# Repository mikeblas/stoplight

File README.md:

# stoplight
This project provides hardware and software for a stoplight controlled by a Raspberry Pi.

## Context
In the late 1990s, I purchased a traffic signal from a curiosities shop. It's a full-scale signal, appropriate for
"real" outdoor use; each lens is about 20cm in diameter, and it's a giant green beast. During the lockdowns in 2020,
I finally found the time to get it working in a fun and useful way.

This project includes a printed circuit board design that hosts a Raspberry Pi Zero W and implements a
mains-based power supply and switching circuits for each of the lamps in the signal. I chose the Pi Zero because
it gets me onto the wireless network, and has enough computing power to do interesting things with the signal. With
a little research, it should be possible to find a smaller board that has WiFi connectivity, but I already had an
unused Pi Zero, so I just went with it.

The board further hosts a generic wireless remote control board built around the PT2272 receiver chip. The chip
gives four latched outputs from a four-button key fob style RF remote. This remote can be used to control
the stoplight.

And of course, the project includes software to make it do something.

## Status

This project is "done enough" for now. All the features below are implemented, and the wish list features are
not yet implemented.

## Hardware Features

The hardware is done; amazingly, I didn't have to re-print the board and got it right on the first try. The
only problem was using a 7805 regulator. The voltage drop made it run red hot, so I replaced it with a three-pin
PC-based switching regulator, which works fine. The filter capacitor on the output of the supply wasn't adequate,
so I increased it. That, of course, required a part with a bigger footprint so the mounting is a bit lumpy,
but it works fine.

## Software Features

The software implements several modes, selectable by the remote. First, we can turn the thing off:

* Turn off the light; minimal processing, nothing illuminated.
* Turn the light back on; whatever mode was active last resumes.

Then, we have one of a few modes active:

* Traffic light. Red, green, yellow, in a realistically timed cycle.
* Random single flash. Flash a single (selectable) lamp at a regular interval.
* Random flash. Flash a randomly selected lamp one at a time.
* Random flash. Flash each lamp at random intervals. This is "disco mode"! 
* Manual selection. Turn a lamp off or on, and it stays that way.

We mostly leave the light in disco mode, and it's fun to see it blinking away.

## Wish List

I'd like to add a few more modes:

* Clock. Flash lights to make a binary time-of-day clock.
* Weather indicator. Show tomorrow's predicted weather (temperature and precipitation)
* Stock market indicator. If the market is open, show the directional change in a particular index.

There's also a couple of interesting things that I'd like to add:

* Mode memory. It would be great to have the system restore its mode when it starts up again after
a reboot or power failure.
* Monitoring. Anything I can monitor in my home network is monitored -- lots of SNMP collectors and
some Influx scripts pull data in to Grafana. Adding 
* Web page. It would be cool to have a little web server to present a UI for changing modes, looking
at statistics, and so on.
* Mobile app. A web API would enable a mobile application for modes and stats, too.

Since the project is built and installed, then I'm not very motivated to work on these things. Maybe
in the winter I'll get another Pi Zero and set it up so I can run the core on my bench, and get to
work on those feature. The design has on-board LEDs for all of the outputs, so pretty much no support
circuitry is necessary. I just need to build and populate one of my spare PC boards. 

## Project Layout

`stoplightd` is the stoplight daemon program. This is the controller that runs on the Pi (as I'm working on it)

`proto` are various fragments and scratch projects as I sort out GPIO, how the hardware works, and try out ideas.

`pcb` is the hardware project for KiCad.

## Images

Installing KiCad just to take a peek is a big ask, so here are some links:

* A snapshot of [the PC board](docs/pics/pc_board.png "PC Board")
* A snapshot of [the schematic](docs/pics/schematic.png "Schematic")

# Dependencies

This project uses [libdaemonize](https://github.com/Aethelflaed/libdaemonize).

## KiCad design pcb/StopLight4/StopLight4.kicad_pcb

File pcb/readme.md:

# Stoplight Controller PC Board

This directory contains different versions of the StopLight PC Board. I split the design since I wasn't comfortable using `git` to manage the projects, and I also wasn't positive I wouldn't fork or rework the older designs anyway. I ended up linear, though, and StopLight4 is the version of the board sent to be fabricated.

## StopLight1

Uses discrete transistors to drive the relays and indicator LEDs.

## StopLight2

Substitutes a `ULN2803` driver chip for the relays to save a lot of space.

## StopLight3

Relays turned out to be pretty noisy, so I built a TRIAC circuit to drive the lights. Maybe the `ULN2803` isn't necessary anymore, but it remains. (Uhoh. Looks like some files are missing!)

## StopLight4

There were fuses on each of the three light lines, which is a bit redundant. Seems nice, but the fuse holders take up a ton of PC board space so I've eliminated them. This resulted in a more pleasing layout and a smaller board. This board version was sent to production.

## StopLight5

This version will fix a few issues, if another production run is needed:

1) Holes in remote header too smaller (0.75mm, should be 1.00mm)
2) Phoenix connectors are facing the wrong way
3) Rotate TP5 so its silk screen matches other TPs
4) Mask over the copper legend for high-voltage outputs
5) "hash" silkscreen over high voltage area of board
6) Renumber F4 to F1

# Hardware PostMortem

Most of the interesting problems are listed above, but some are not; and some are interesting to investigate a little more.

## Power Supply

Most of the issues were with the power supply, really.

**Power Budget**. I just figured I'd get a transformer, rectifier, a couple of filter caps, and drive a 7805 and be done. It's a little more complicated than that. First off, I bugeted a bit high for power because I thought I would be holding relays up. Once I eliminated the relays, I shouldn't made a closer estimate. The supply should drive about 1.5 amps without a problem (except for heat), and I could use a much smaller transformer since my budget is really closer to 500 milliamps.

**Filter**. I couldn't find good advice about sizing the filter caps, and they're too small. Maybe the over-arching problem is that I didn't prototype the power supply on my breadboard. Had I done so, I would've caught most (if not all) of these problems.

**Heat**. My transformer develops 10 volts at the secondary, which initially sounded low. The dropout of the regulator means I need at least 7 volts at the input, and I'm making lots of heat in the linear regulator. A switching regulator is probably the best solution, and I'm probably going to end up getting one of the "cheater" switching converters on a TO-220-sized board to solve the heat issue.

## Layout

I'm pretty pleased with the layout. I was always tempted to "hide" components under the Raspberry Pi module, but I'm glad I didn't because it would  have made troubleshooting harder. Getting a probe onto anything under there would be obnoxious -- my only choice would be to get to the back of the board.

After that, the layout is pretty nice. I'm glad I got rid of the redundant fuses. It might have helped more the use an in-line fuse holder, but those also have some inconveniences. A smaller fuse form factor might have been a good idea, tho.

## In General

It was great to get rid of the relays. The clicking was completely obnoxious; I can't imagine these being used in anything but an industrial or large commercial application. Learning how to control the TRIACS was fun. 

I could probably get rid of the driver, but it's not much real estate and gives me a bit more confidence in the design for now.

## Software

The software is going well, though I don't have as much time to spend on it. When I do, I'm productive and can get some things done.

## Mechanical

The mechanical assembly came together quite well, and I'm happy with it. Even the carpentry isn't so bad.

## Light Bulbs

I'm worried that the light is too bright. Maybe a cool V2 feature would be to support PWM dimming so the brightness would be settable through software. Choosing bulbs was hard; there aren't many incadescent choices anymore. LED bulbs don't go so dim, either. The 25-watt equivalent LED bulb seems best, but it's quite expensive (about $8) and who knows how long they'll make it. A couple LED bulbs I tried didn't turn on or off correctly, so experimenting is kind of hit-and-miss.

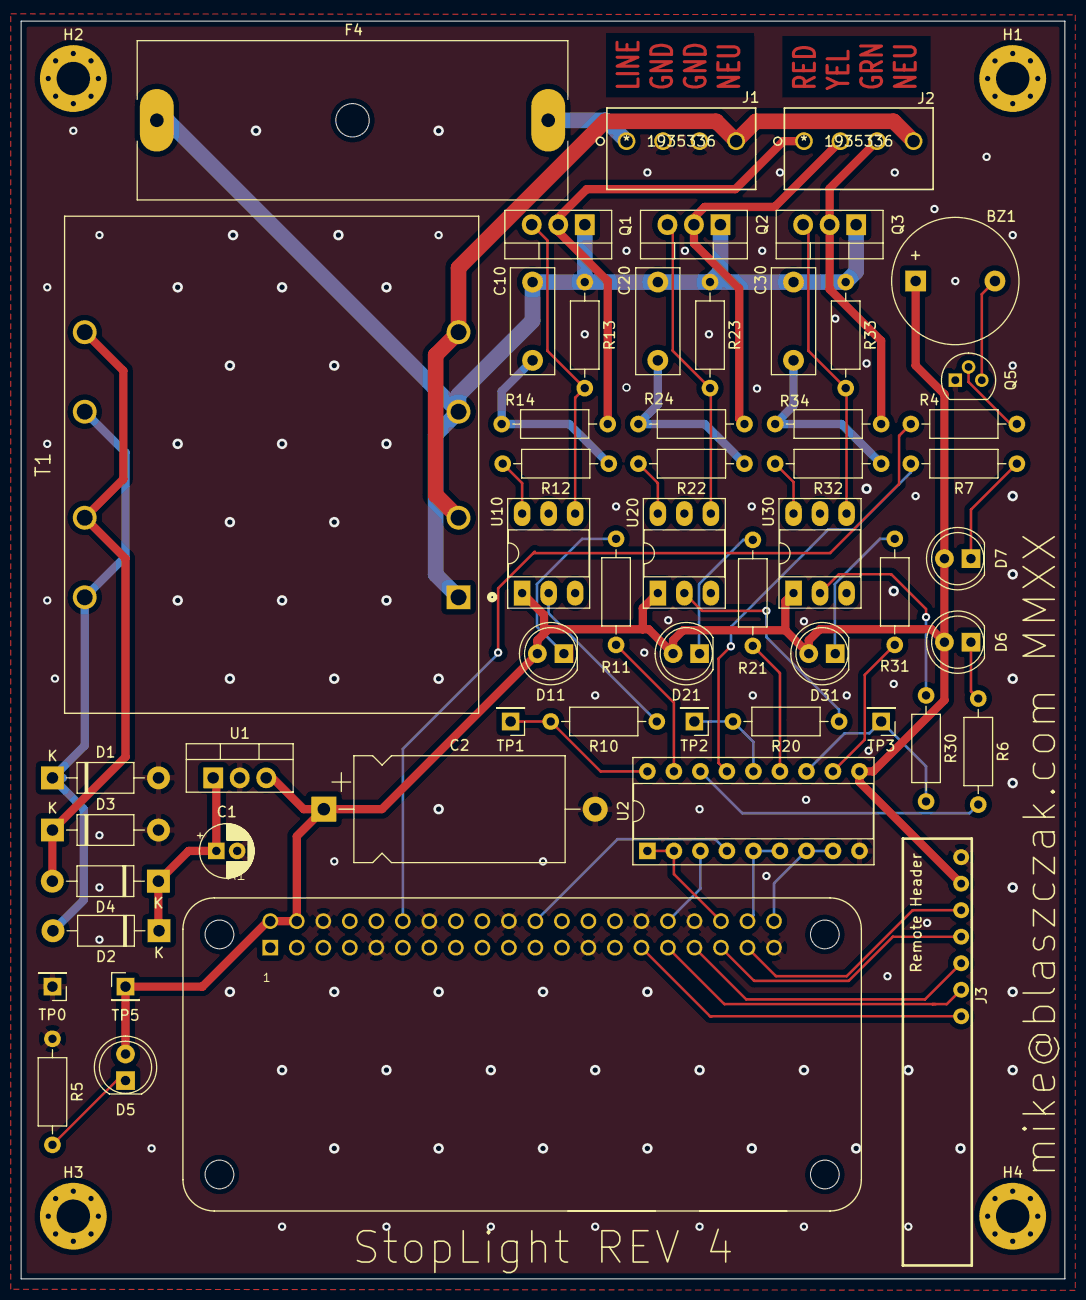
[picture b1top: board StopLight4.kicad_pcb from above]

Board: 2 copper layers, 100.0 x 120.5 mm, 59 parts (0 on the bottom side), 50 nets.

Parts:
A1: ADA3708; ADA3708_RPI-ZERO
BZ1: Buzzer; Buzzer_12x9.5RM7.6
C1: 3.3uF; CP_Radial_D5.0mm_P2.00mm
C2: 220uF 50v; CP_Axial_L20.0mm_D10.0mm_P26.00mm_Horizontal
C10, C20, C30: 0.033uF; C_Rect_L10.0mm_W4.0mm_P7.50mm_MKS4
D1, D2, D3, D4: 1N4002; D_DO-41_SOD81_P10.16mm_Horizontal
D5, D6, D7, D11, D21, D31: LED; LED_D5.0mm
F4: Fuse; Fuseholder_Cylinder-6.3x32mm_Schurter_0031-8002_Horizontal_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
H1, H2, H3, H4: MountingHole; MountingHole_3.2mm_M3_Pad_Via
J1, J2: 1935336; 1984633
J3: Remote Header; WirelessRemote
Q1, Q2, Q3: BT136-600; TO-220-3_Vertical
Q5: 2N3904; TO-92
R4: 10R3; R_Axial_DIN0207_L6.3mm_D2.5mm_P10.16mm_Horizontal
R5, R6, R7, R10, R11, R20, R21, R30, R31: 220R; R_Axial_DIN0207_L6.3mm_D2.5mm_P10.16mm_Horizontal
R12, R22, R32: 150R; R_Axial_DIN0207_L6.3mm_D2.5mm_P10.16mm_Horizontal
R13, R23, R33: 390R; R_Axial_DIN0207_L6.3mm_D2.5mm_P10.16mm_Horizontal
R14, R24, R34: 51R; R_Axial_DIN0207_L6.3mm_D2.5mm_P10.16mm_Horizontal
T1: FS20-600; XFMR_FS20-600
TP0, TP1, TP2, TP3, TP5: Conn_01x01_Male; PinHeader_1x01_P2.54mm_Vertical
U1: L7805; TO-220-3_Vertical
U2: ULN2803A; DIP-18_W7.62mm_Socket
U10, U20, U30: MOC3021M; DIP-6_W7.62mm_Socket_LongPads

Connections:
/D0: A1.37, J3.5
/D1: A1.35, J3.4
/D2: A1.33, J3.3
/D3: A1.31, J3.2
/GRN: A1.40, U2.7, U2.8
/IND1: A1.32, U2.3
/IND2: A1.22, U2.4
/RED: A1.36, U2.1, U2.2
/VT: A1.29, J3.1
/YEL: A1.38, U2.5, U2.6
BZZ: A1.12, R4.2
GND: A1.6, A1.9, A1.14, A1.20, A1.25, A1.30, A1.34, A1.39, C1.2, C2.2, D1.2, D3.2, J1.2, J1.3, J3.7, Q5.1, R5.1, TP0.1, U1.2, U2.9
LINE: C10.2, C20.2, C30.2, F4.1, Q1.1, Q2.1, Q3.1, R13.1, R23.1, R33.1, T1.1, T1.3
NEUT: J1.4, J2.4, T1.2, T1.4
unnamed: BZ1.2, Q5.3
unnamed: C1.1, D2.1, D4.1, U1.1
unnamed: C10.1, R12.1, R14.2
unnamed: C20.1, R22.1, R24.2
unnamed: C30.1, R32.1, R34.2
unnamed: D1.1, D2.2, T1.5, T1.7
unnamed: D3.1, D4.2, T1.6, T1.8
unnamed: D5.1, R5.2
unnamed: D6.1, R6.1
unnamed: D7.1, R7.1
unnamed: D11.1, R11.1
unnamed: D21.1, R21.1
unnamed: D31.1, R31.1
unnamed: J2.1, Q1.2, R14.1
unnamed: J2.2, Q2.2, R24.1
unnamed: J2.3, Q3.2, R34.1
unnamed: Q1.3, R13.2, U10.4
unnamed: Q2.3, R23.2, U20.4
unnamed: Q3.3, R33.2, U30.4
unnamed: Q5.2, R4.1
unnamed: R6.2, U2.16
unnamed: R7.2, U2.15
unnamed: R10.1, U10.2
unnamed: R10.2, TP1.1, U2.18
unnamed: R11.2, U2.17
unnamed: R12.2, U10.6
unnamed: R20.1, U20.2
unnamed: R20.2, TP2.1, U2.14
unnamed: R21.2, U2.13
unnamed: R22.2, U20.6
unnamed: R30.1, U30.2
unnamed: R30.2, TP3.1, U2.12
unnamed: R31.2, U2.11
unnamed: R32.2, U30.6
VAC: F4.2, J1.1
VCC: A1.2, A1.4, BZ1.1, C2.1, D5.2, D6.2, D7.2, D11.2, D21.2, D31.2, J3.6, TP5.1, U1.3, U2.10, U10.1, U20.1, U30.1

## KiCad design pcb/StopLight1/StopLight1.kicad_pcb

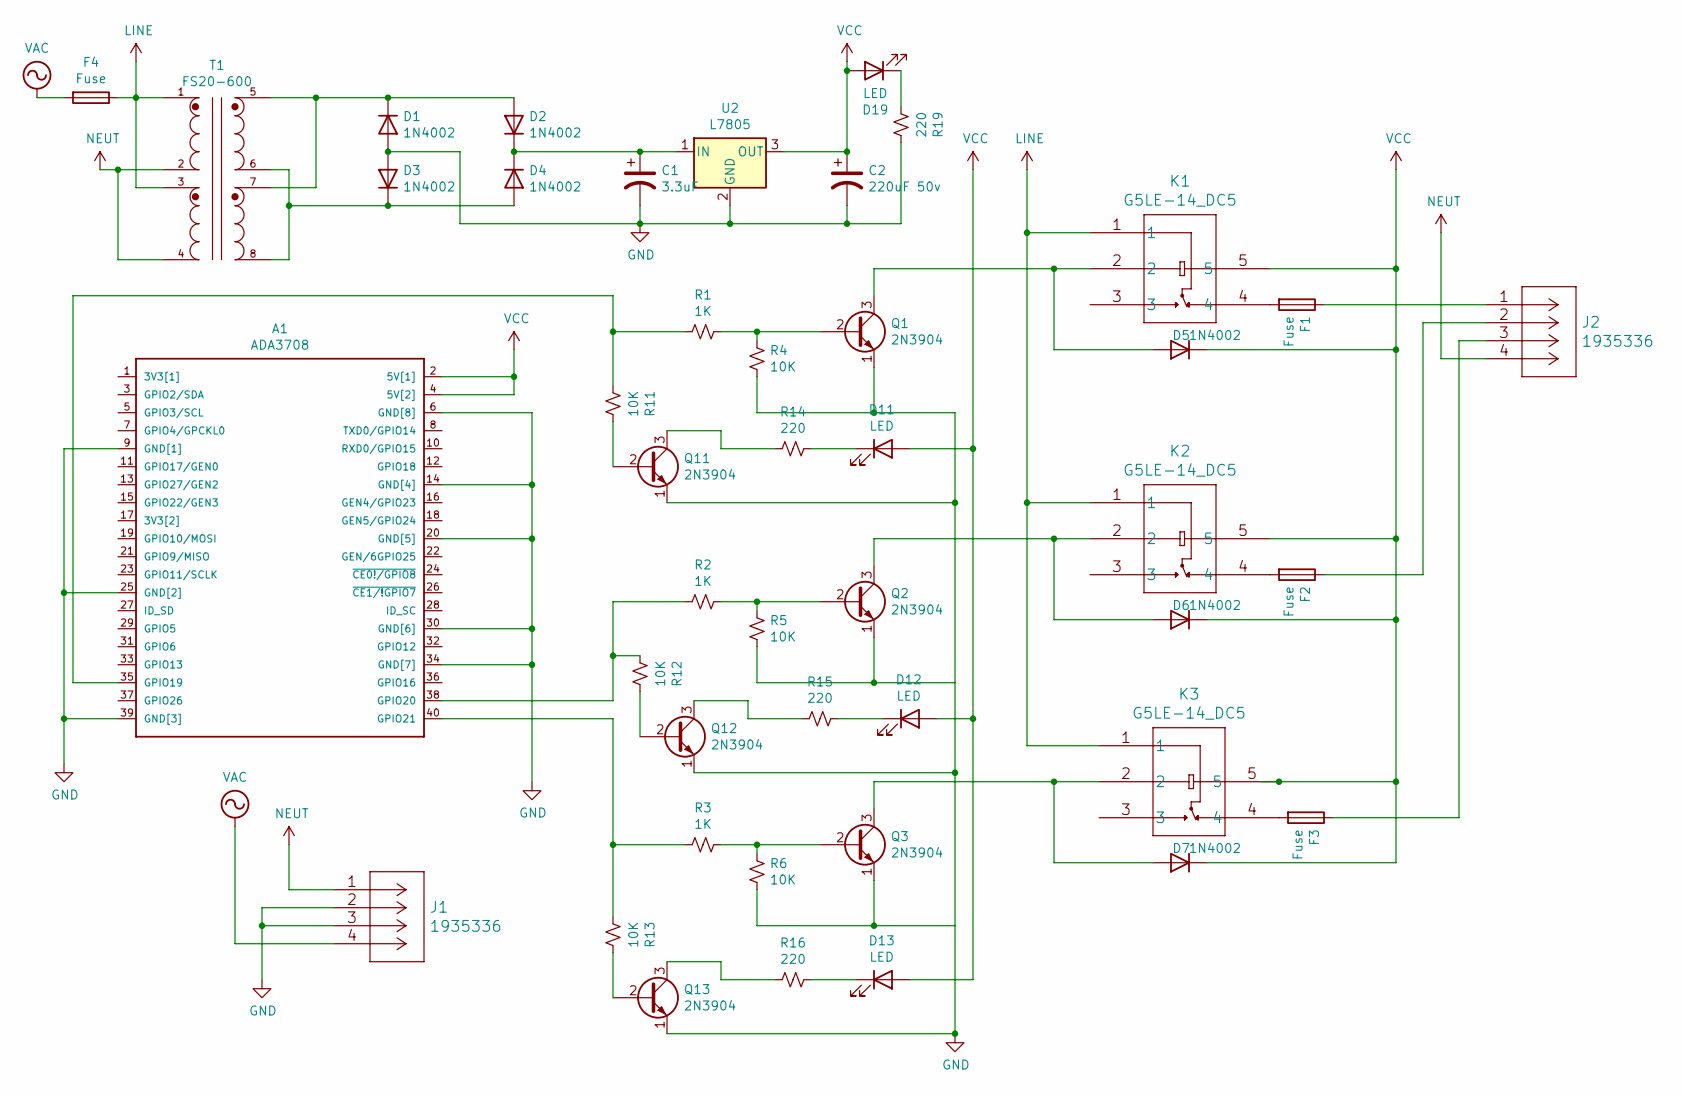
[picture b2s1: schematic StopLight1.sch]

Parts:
A1: ADA3708; ADA3708_RPI-ZERO
C1: 3.3uF; CP_Radial_D5.0mm_P2.00mm
C2: 220uF 50v; CP_Axial_L20.0mm_D10.0mm_P26.00mm_Horizontal
D1, D2, D3, D4, D5, D6, D7: 1N4002; D_DO-41_SOD81_P10.16mm_Horizontal
D11, D12, D13, D19: LED; LED_D5.0mm
F1, F2, F3, F4: Fuse; Fuseholder_Cylinder-6.3x32mm_Schurter_0031-8002_Horizontal_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
J1, J2: 1935336
K1, K2, K3: G5LE-14_DC5; G5LE-14 DC5
Q1, Q2, Q3, Q11, Q12, Q13: 2N3904; TO-92
R1, R2, R3: 1K; R_Axial_DIN0207_L6.3mm_D2.5mm_P10.16mm_Horizontal
R4, R5, R6, R11, R12, R13: 10K; R_Axial_DIN0207_L6.3mm_D2.5mm_P10.16mm_Horizontal
R14, R15, R16, R19: 220; R_Axial_DIN0207_L6.3mm_D2.5mm_P10.16mm_Horizontal
T1: FS20-600; XFMR_FS20-600
U2: L7805; TO-220-3_Vertical

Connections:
GND: A1.6 (GND[8]), A1.9 (GND[1]), A1.14 (GND[4]), A1.20 (GND[5]), A1.25 (GND[2]), A1.30 (GND[6]), A1.34 (GND[7]), A1.39 (GND[3]), C1.2, C2.2, D1.2 (A), D3.2 (A), J1.2, J1.3, Q1.1 (E), Q11.1 (E), Q12.1 (E), Q13.1 (E), R4.2, R19.1, U2.2 (GND)
LINE: F4.1, K1.1, K2.1, K3.1, T1.1, T1.3
NEUT: J1.1, J2.4, T1.2, T1.4
unnamed: A1.35 (GPIO19), R1.2, R11.2
unnamed: A1.38 (GPIO20), R2.2, R12.2
unnamed: A1.40 (GPIO21), R3.2, R13.2
unnamed: C1.1, D2.1 (K), D4.1 (K), U2.1 (IN)
unnamed: D1.1 (K), D2.2 (A), T1.5, T1.7
unnamed: D3.1 (K), D4.2 (A), T1.6, T1.8
unnamed: D5.2 (A), K1.2, Q1.3 (C)
unnamed: D6.2 (A), K2.2, Q2.3 (C)
unnamed: D7.2 (A), K3.2, Q3.3 (C)
unnamed: D11.1 (K), R14.1
unnamed: D12.1 (K), R15.1
unnamed: D13.1 (K), R16.1
unnamed: D19.1 (K), R19.2
unnamed: F1.1, J2.1
unnamed: F1.2, K1.4
unnamed: F2.1, J2.2
unnamed: F2.2, K2.4
unnamed: F3.1, J2.3
unnamed: F3.2, K3.4
unnamed: Q1.2 (B), R1.1, R4.1
unnamed: Q2.1 (E), R5.2
unnamed: Q2.2 (B), R2.1, R5.1
unnamed: Q3.1 (E), R6.2
unnamed: Q3.2 (B), R3.1, R6.1
unnamed: Q11.2 (B), R11.1
unnamed: Q11.3 (C), R14.2
unnamed: Q12.2 (B), R12.1
unnamed: Q12.3 (C), R15.2
unnamed: Q13.2 (B), R13.1
unnamed: Q13.3 (C), R16.2
VAC: F4.2, J1.4
VCC: A1.2 (5V[1]), A1.4 (5V[2]), C2.1, D5.1 (K), D6.1 (K), D7.1 (K), D11.2 (A), D12.2 (A), D13.2 (A), D19.2 (A), K1.5, K2.5, K3.5, U2.3 (OUT)

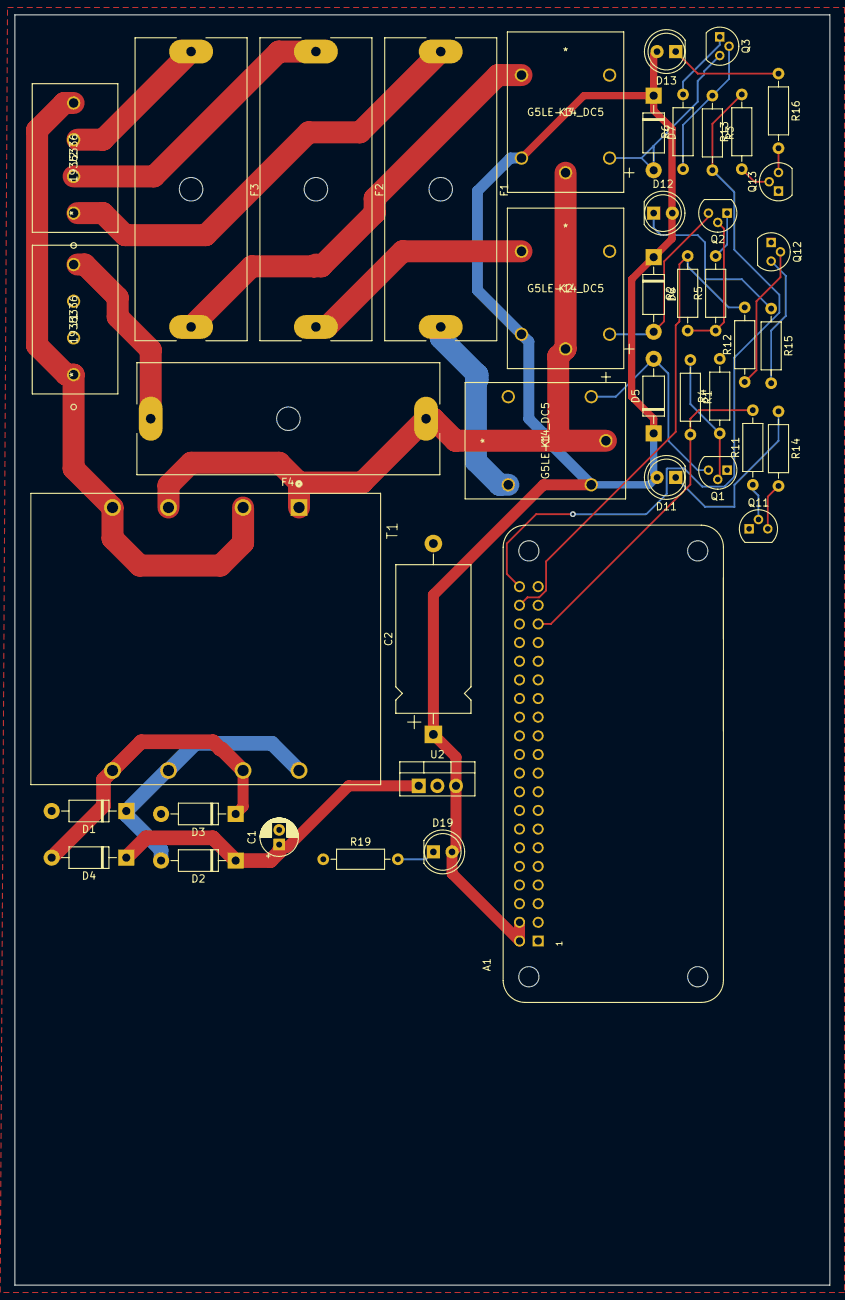
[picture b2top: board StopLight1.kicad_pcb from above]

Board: 2 copper layers, 111.0 x 173.0 mm, 44 parts (0 on the bottom side), 35 nets.

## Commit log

2020-09-03 get something into the readme
2020-09-03 add PCB projects
2020-09-03 add first GPIO app
2020-09-03 first cut at remote reading
2020-09-03 only show when change detected
2020-09-04 try using wait functions for remote input
2020-09-06 remove commented code
2020-09-06 add flick program
2020-09-06 PC Board design is getting close
2020-09-09 Smaller PCB, sent to production!
2020-09-09 add readme files, restructure directories
2020-09-09 delay to let remote inputs stabilize
2020-09-09 controllable with remote
2020-09-09 beep feedback
2020-09-10 tighten up makefiles
2020-09-10 add gitignore files
2020-09-11 first cut at a daemon
2020-09-13 turn on warnings, fix them up
2020-09-13 note dependency
2020-09-17 setup stoplightd daemon project
2020-09-17 readme about the plan
2020-09-17 handle press/release in framework loop
2020-09-17 one step closer
2020-09-17 cleanup, fix gitignore
2020-09-17 update readme, refactor modelinterface header
2020-09-17 fix gitignore, clean up makefile a bit
2020-09-17 add selector mode for testing; some makefile tweaks
2020-09-17 refactor daemon itself, fix up makefile, split function
2020-09-17 fix stoplightd indentation
2020-09-17 makefile enhancements
2020-09-18 general refactor; prepare for menu implementation
2020-09-18 log during startup
2020-09-18 add modefactory, hook up mode switching (almost works)
2020-09-18 mode switching mostly works
2020-09-18 hook up remote mode
2020-09-18 cleanup, reset lights between modes
2020-09-19 fix key rollover when waking up from idle
2020-09-21 add beeps on idle and selector mode transitions
2020-09-21 add signal handling from daemonize library
2020-09-22 figuring out how dtor works?
    looks like there's a bit of a misunderstanding here. The derived
    class dtor will be called when the fork quits the parent process,
    leaving the forked process running around ...
2020-09-23 update PCB readme with some notes
2020-09-30 change buzzer to match PCB; generate assembly listings
    just curious about output assembly, so make listings
2020-10-01 Update readme.md
    postmortem notes
2020-10-01 add C button to regular mode to select speed
2020-10-01 move object files to dir
2020-10-01 makefile handles directories fully, update gitignore
2020-10-01 fix indentation, spacing in lights.h
2020-10-01 add support for indexed toggling, indicator lights
2020-10-01 add flickermode
2020-10-01 remember to set indicators as outputs
2020-10-09 don't double-free stoplightd members after fork
2020-11-06 fix typo
2020-11-06 remove unused function
2020-12-04 get clock mode started; Lights class enhancements
2020-12-04 chirping clock works!
2020-12-05 adjust clock behaviour to one light each quarter, all lights on hour
2020-12-05 twiddle Indicator 2 during main loop
2020-12-05 add comparitor to switch between seconds in minutes in clock mode
    this makes testing easier (for the less patient)
2020-12-06 finish clock mode!
2021-02-03 setup service install
    add a service file, install target to makefile
    switch around pid file name
2022-07-21 Notes about controller
2022-07-21 update docs and status, add pictures
2022-12-26 add libdaemonize notes to stoplightd readme
2022-12-26 addd libgpiod to the readme
2022-12-28 get web status request working
2022-12-28 switch modes from web API

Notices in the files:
parts and their libraries:
Copyright 2016 Accelerated Designs. All rights reserved.
